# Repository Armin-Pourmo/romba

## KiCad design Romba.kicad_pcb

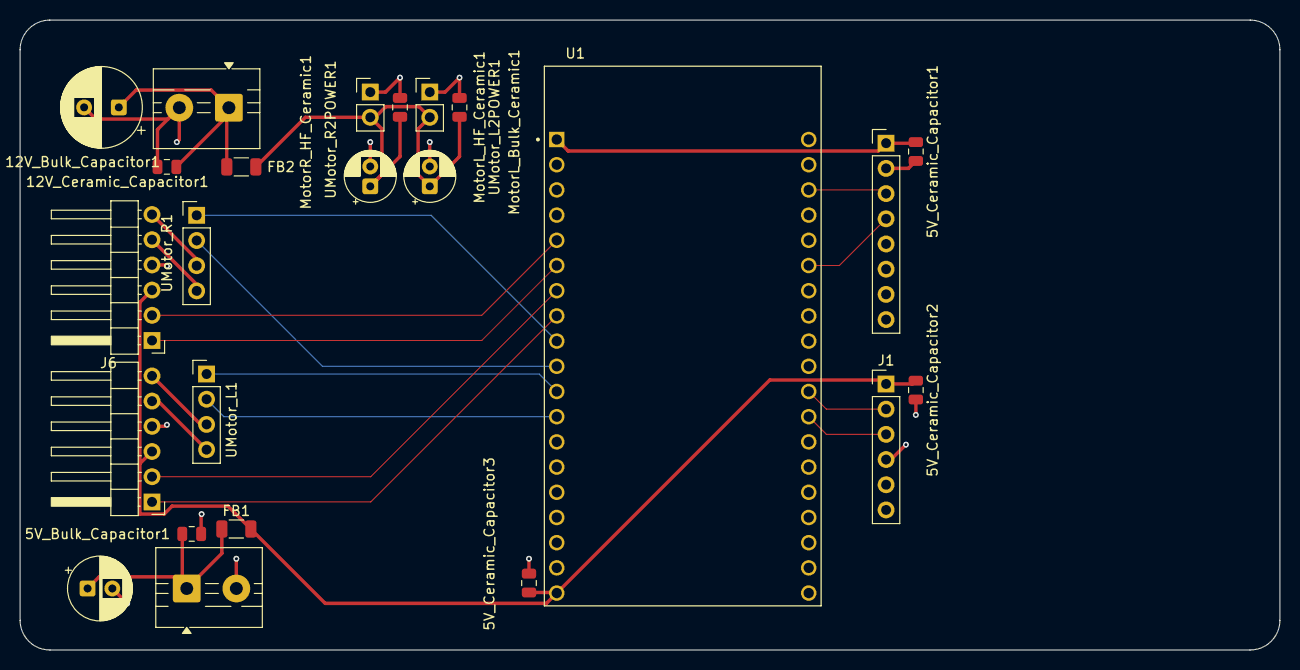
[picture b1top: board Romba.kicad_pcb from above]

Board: 2 copper layers, 127.0 x 63.5 mm, 24 parts (0 on the bottom side), 22 nets.

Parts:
5V_Bulk_Capacitor1: ~470 microFarads; CP_Radial_D6.3mm_P2.50mm
5V_Ceramic_Capacitor1, 5V_Ceramic_Capacitor2, 5V_Ceramic_Capacitor3, 5V_Ceramic_Capacitor4, 12V_Ceramic_Capacitor1: .1 microFarads; C_0805_2012Metric
12V_Bulk_Capacitor1: ~1000 microFarads; CP_Radial_D8.0mm_P3.50mm
FB1, FB2: FerriteBead; R_1206_3216Metric
J1: LIDAR UART; PinHeader_1x06_P2.54mm_Vertical
J2: Gyro; PinHeader_1x08_P2.54mm_Vertical
J3: 5v-Bus; TerminalBlock_MaiXu_MX126-5.0-02P_1x02_P5.00mm
J4: 12V-Bus; TerminalBlock_MaiXu_MX126-5.0-02P_1x02_P5.00mm
J5: Motor_L; PinHeader_1x06_P2.54mm_Horizontal
J6: Motor_R; PinHeader_1x06_P2.54mm_Horizontal
MotorL_Bulk_Ceramic1: 47 microFarads; CP_Radial_D5.0mm_P2.00mm
MotorL_HF_Ceramic1: .1 microFarads; C_0805_2012Metric
MotorR_Bulk_Ceramic1: 47 microFarads; CP_Radial_D5.0mm_P2.00mm
MotorR_HF_Ceramic1: .1 microFarads; C_0805_2012Metric
U1: ESP32-DEVKITC-32D; MODULE_ESP32-DEVKITC-32D
UMotor_L1: DRV8871DDA; PinHeader_1x04_P2.54mm_Vertical
UMotor_L2POWER1: DRV8871DDA; PinHeader_1x02_P2.54mm_Vertical
UMotor_R1: DRV8871DDA; PinHeader_1x04_P2.54mm_Vertical
UMotor_R2POWER1: DRV8871DDA; PinHeader_1x02_P2.54mm_Vertical

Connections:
+3.3V: 5V_Ceramic_Capacitor1.1, J2.1, U1.J2-1 (3V3)
+5V: 5V_Ceramic_Capacitor2.1, 5V_Ceramic_Capacitor3.1, FB1.2, J1.1, J5.3, J6.3, U1.J2-19 (EXT_5V)
+12V: FB2.2, MotorL_Bulk_Ceramic1.1, MotorL_HF_Ceramic1.1, MotorR_Bulk_Ceramic1.1, MotorR_HF_Ceramic1.1, UMotor_L2POWER1.5 (VM), UMotor_R2POWER1.5 (VM)
/5V_Bus: 5V_Bulk_Capacitor1.1, 5V_Ceramic_Capacitor4.1, FB1.1, J3.1
/12V_Bus: 12V_Bulk_Capacitor1.1, 12V_Ceramic_Capacitor1.1, FB2.1, J4.1
/EncoderA_L: J5.1, U1.J2-8 (IO33)
/EncoderA_R: J6.1, U1.J2-6 (IO35)
/EncoderB_L: J5.2, U1.J2-7 (IO32)
/EncoderB_R: J6.2, U1.J2-5 (IO34)
/Gyro_SCL\Rx: J2.3, U1.J3-3 (IO22)
/Gyro_SDA\Tx: J2.4, U1.J3-6 (IO21)
/LiDAR_RXD/SDA: J1.2, U1.J3-11 (IO17)
/LiDAR_TXD\SCL: J1.3, U1.J3-12 (IO16)
/ML+: J5.6, UMotor_L1.3 (IN1)
/ML-: J5.5, UMotor_L1.4 (ILIM)
/MR+: J6.6, UMotor_R1.3 (IN1)
/MR-: J6.5, UMotor_R1.4 (ILIM)
/PWM1_L: U1.J2-11 (IO27), UMotor_L1.1 (GND)
/PWM1_R: U1.J2-9 (IO25), UMotor_R1.1 (GND)
/PWM2_L: U1.J2-12 (IO14), UMotor_L1.2 (IN2)
/PWM2_R: U1.J2-10 (IO26), UMotor_R1.2 (IN2)
GND: 5V_Bulk_Capacitor1.2, 5V_Ceramic_Capacitor1.2, 5V_Ceramic_Capacitor2.2, 5V_Ceramic_Capacitor3.2, 5V_Ceramic_Capacitor4.2, 12V_Bulk_Capacitor1.2, 12V_Ceramic_Capacitor1.2, J1.4, J2.2, J3.2, J4.2, J5.4, J6.4, MotorL_Bulk_Ceramic1.2, MotorL_HF_Ceramic1.2, MotorR_Bulk_Ceramic1.2, MotorR_HF_Ceramic1.2, U1.J2-14 (GND1), U1.J3-1 (GND3), U1.J3-7 (GND2), UMotor_L2POWER1.1 (GND), UMotor_R2POWER1.1 (GND)

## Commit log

2025-12-22 Initial Romba KiCad project
2025-12-22 Added Resource Images
2025-12-22 Updated Docs
2025-12-25 Holy Headache added most footprints
2026-01-12 chickenmcnegus
2026-01-12 Work done on PCB Traces
2026-01-12 New Branch
2026-01-12 It's all gone
2026-01-12 please be all gone
2026-01-13 a bit lost
2026-01-13 fixed libraries
2026-01-13 Fixed library issue good to start routing
2026-01-13 Updated PCB Layout to more optimal state
2026-01-15 Finished PCB Routing
2026-01-16 New folder for Code
